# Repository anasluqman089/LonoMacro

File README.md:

# LonoMacro

LonoMacro is a modular macro keypad built around three XIAO nRF52840 boards:
an OLED-equipped master, a keypad slave, and a rotary-encoder slave. The master
connects to a computer over USB-C and to the slaves over Bluetooth Low Energy
(BLE). Slave inputs are forwarded to the computer as USB keyboard events.

## Project files

- [`PCB/`](PCB/) — KiCad schematic, PCB layout, and project files.
- [`CAD/`](CAD/) — 3D STEP models.
- [`Production/`](Production/) — Gerber, drill, and STL manufacturing files.
- [`firmware/`](firmware/) — Arduino sketches for the master and both slaves.
- [`BOM.csv`](BOM.csv) — Bill of materials, prices, and supplier search links.

## Firmware setup

Install the ArduinoBLE, Adafruit GFX, and Adafruit SSD1306 libraries. Select a
XIAO nRF52840 Arduino board package that supports USB keyboard output for the
master. Compile and upload the corresponding sketch to each board:

- [OLED master](firmware/OLED_Master/OLED_Master.ino)
- [Keypad slave](firmware/Keypad_Slave/Keypad_Slave.ino)
- [Rotary slave](firmware/Rotary_Slave/Rotary_Slave.ino)

The master expects an SSD1306 I2C OLED at address `0x3C`.

## Pairing and controls

1. Connect the OLED master to the computer over USB-C.
2. Press the 6 mm pairing button on each slave: SW5 on the keypad and SW7 on
   the rotary encoder. The corresponding slave LED blinks while it advertises.
3. Press the 6 mm pairing/connect button on the master (SW8). The master LED
   blinks while it searches, and the OLED shows each slave's connection status.
   When both slaves are connected, the master LED and both slave LEDs stay on.
4. Press SW1–SW4 to send the number keys `1`–`4`. Rotate the encoder to send
   Up/Down arrow keys; press the encoder (SW6) to send Enter.

The master LED is solid when both slaves are connected and pulses when it
receives an input. A connected slave LED is solid and pulses when it sends an
input. If a slave disconnects, press its pairing button and then press SW8 on
the master to reconnect.

## OLED and battery status

The OLED-equipped master is intended to show the connected macropads and their
battery levels. A future status screen could include the time and date, for
example:

```text
10:00 PM              1/11/26
----------------------------
Rotary Encoder          50%
Keypad                   5%
```

The current firmware displays connection status and recent input events; it
does not yet report slave battery levels or show a clock. Battery reporting and
time display will require additional firmware and, for the clock, a time source.
The master can be powered from the computer's USB-C connection. The slave
macropads are intended to use lithium-ion batteries; battery and charging
hardware should be selected to match the final design.

## Bill of materials

Prices are the listed prices per BOM row, including grouped quantities. They
are estimates, may change, and **do not include shipping**. The case price is
approximate; purchase links are supplier search pages.

| Component | Qty | Real Unit Price (USD) | Total Market Price (USD) | Reference Links |
| :--- | :---: | :---: | :---: | :--- |
| **XIAO-nRF52840** (Standard) | 3 | \$9.99 | **\$29.97** | [Search AliExpress](https://www.aliexpress.com/w/wholesale-XIAO-nRF52840.html) |
| **Cherry MX Keyboard Switch** | 4 | \$0.60 | **\$2.40** | [Search AliExpress](https://www.aliexpress.com/w/wholesale-Cherry-MX-keyboard-switch.html) |
| **1.3 Inch OLED Screen** | 1 | \$4.00 | **\$4.00** | [Search AliExpress](https://www.aliexpress.com/w/wholesale-1.3-Inch-OLED-Screen.html) |
| **Rotary Encoder EC11** | 1 | \$0.50 | **\$0.50** | [Search AliExpress](https://www.aliexpress.com/w/wholesale-Rotary-Encoder.html) |
| **5mm LED** | 3 | \$0.10 | **\$0.30** | [Search AliExpress](https://www.aliexpress.com/w/wholesale-5mm-LED.html) |
| **01x02 JST PH Connector** | 3 | \$0.15 | **\$0.45** | [Search AliExpress](https://www.aliexpress.com/w/wholesale-01x02-JST-PH-Connector.html) |
| **220 Film Resistor** | 3 | \$0.05 | **\$0.15** | [Search AliExpress](https://www.aliexpress.com/w/wholesale-220-Film-Resistor.html) |
| **6 mm THT Switch** | 3 | \$0.10 | **\$0.30** | [Search AliExpress](https://www.aliexpress.com/w/wholesale-6-mm-THT-switch.html) |
| **01x04 Pin Header** | 1 | \$0.20 | **\$0.20** | [Search AliExpress](https://www.aliexpress.com/w/wholesale-01x04-Pin-Header.html) |
| **PCB Fabrication** | 1 | \$12.00 | **\$12.00** | — |
| **3D Printed Case** | 1 | \$15.00 | **\$15.00** | — |
| **Estimated Real Total** | | | **~\$65.27** | |

## CAD

[Open the LonoMacro Onshape document](https://cad.onshape.com/documents/b238660379d2ad484aa23eea/w/9873678c9d89b1b19152732d/e/ca0627a1691ab6fd1505dec4).

## Image 

### Scematic

### PCB

### CAD

## Extra

This project is made for Fabricate, a YSWS program by Hack Club

[Project](https://fabricate.hackclub.com/projects/699).

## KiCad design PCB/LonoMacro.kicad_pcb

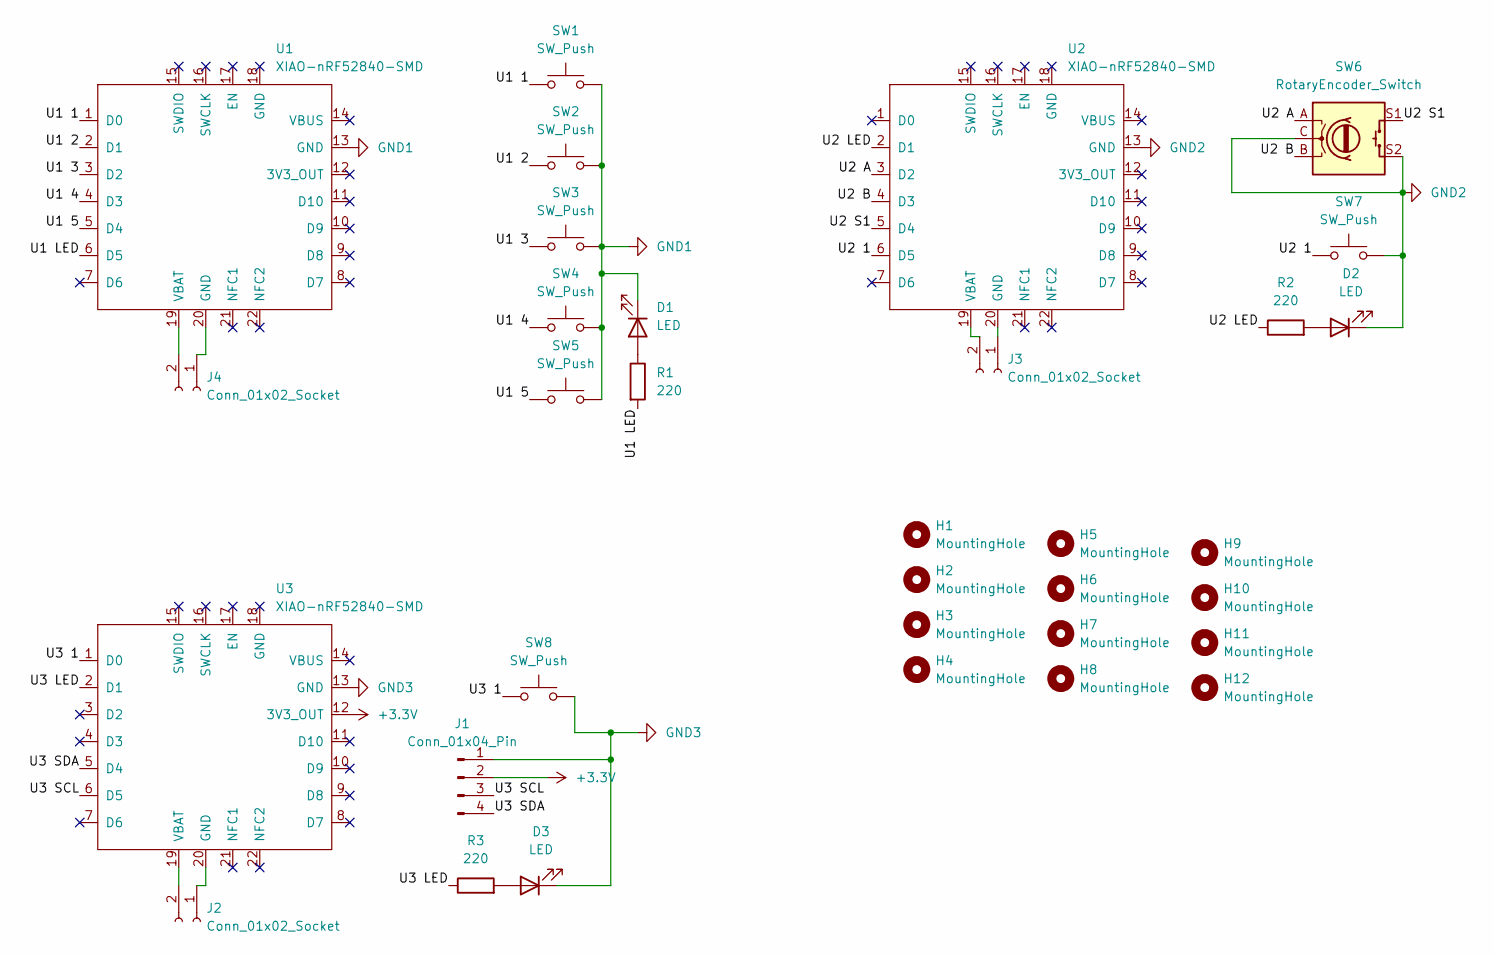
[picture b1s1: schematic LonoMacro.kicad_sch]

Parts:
D1, D2, D3: LED; LED_D5.0mm
H1, H2, H3, H4, H5, H6, H7, H8, H9, H10, H11, H12: MountingHole; MountingHole_2.2mm_M2
J1: Conn_01x04_Pin; PinHeader_1x04_P2.54mm_Vertical
J2, J3, J4: Conn_01x02_Socket; JST_PH_S2B-PH-K_1x02_P2.00mm_Horizontal
R1, R2, R3: 220; R_Axial_DIN0207_L6.3mm_D2.5mm_P7.62mm_Horizontal
SW1, SW2, SW3, SW4: SW_Push; SW_Cherry_MX_1.00u_PCB
SW5, SW7, SW8: SW_Push; SW_PUSH_6mm
SW6: RotaryEncoder_Switch; RotaryEncoder_Alps_EC11E-Switch_Vertical_H20mm
U1, U2, U3: XIAO-nRF52840-SMD

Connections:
+3.3V: J1.2, U3.12 (3V3_OUT)
/U1 1: SW1.1, U1.1 (D0)
/U1 2: SW2.1, U1.2 (D1)
/U1 3: SW3.1, U1.3 (D2)
/U1 4: SW4.1, U1.4 (D3)
/U1 5: SW5.1, U1.5 (D4)
/U1 LED: R1.2, U1.6 (D5)
/U2 1: SW7.1, U2.6 (D5)
/U2 A: SW6.A, U2.3 (D2)
/U2 B: SW6.B, U2.4 (D3)
/U2 LED: R2.1, U2.2 (D1)
/U2 S1: SW6.S1, U2.5 (D4)
/U3 1: SW8.1, U3.1 (D0)
/U3 LED: R3.1, U3.2 (D1)
/U3 SCL: J1.3, U3.6 (D5)
/U3 SDA: J1.4, U3.5 (D4)
GND1: D1.1 (K), SW1.2, SW2.2, SW3.2, SW4.2, SW5.2, U1.13 (GND)
GND2: D2.1 (K), SW6.C, SW6.S2, SW7.2, U2.13 (GND)
GND3: D3.1 (K), J1.1, SW8.2, U3.13 (GND)
unnamed: D1.2 (A), R1.1
unnamed: D2.2 (A), R2.2
unnamed: D3.2 (A), R3.2
unnamed: J2.1, U3.20 (GND)
unnamed: J2.2, U3.19 (VBAT)
unnamed: J3.1, U2.20 (GND)
unnamed: J3.2, U2.19 (VBAT)
unnamed: J4.1, U1.20 (GND)
unnamed: J4.2, U1.19 (VBAT)

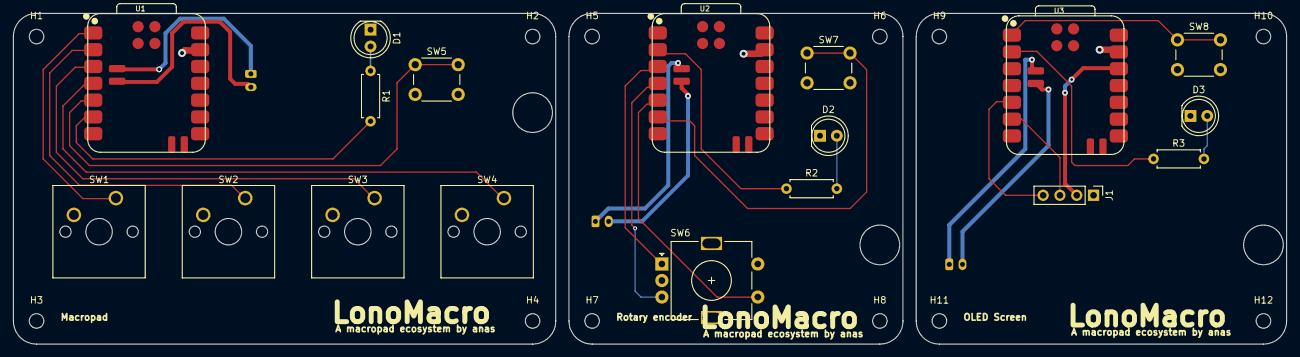
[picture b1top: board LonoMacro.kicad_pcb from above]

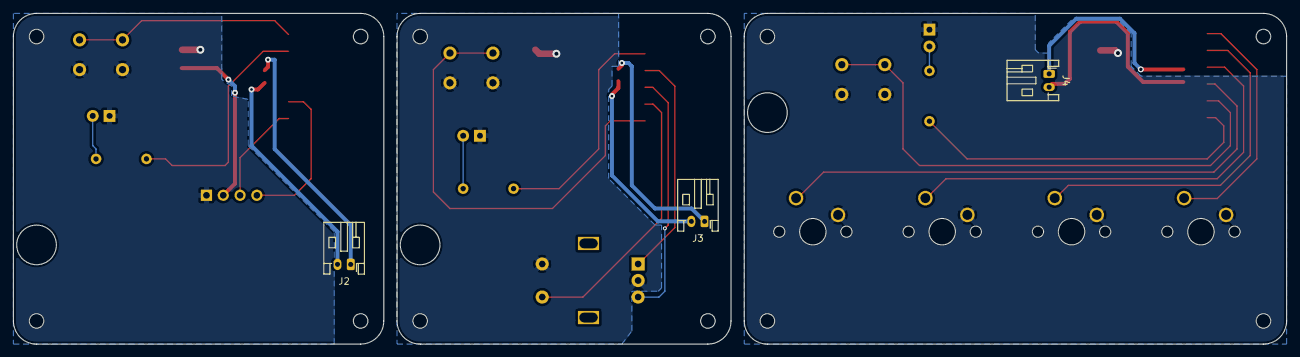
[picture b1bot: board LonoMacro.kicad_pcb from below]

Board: 2 copper layers, 192.5 x 50.0 mm, 33 parts (3 on the bottom side), 28 nets.

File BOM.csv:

"Reference","Quantity","Name","Price","Buy Link"
"D1,D2,D3","3","5mm LED","$0.30","https://www.aliexpress.com/w/wholesale-5mm-LED.html"
"J1","1","01x04 Pin Header","$0.20","https://www.aliexpress.com/w/wholesale-01x04-Pin-Header.html"
"J2,J3,J4","3","01x02 JST PH Connector","$0.45","https://www.aliexpress.com/w/wholesale-01x02-JST-PH-Connector.html"
"R1,R2,R3","3","220 Film Resistor","$0.15","https://www.aliexpress.com/w/wholesale-220-Film-Resistor.html"
"SW1,SW2,SW3,SW4","4","Cherry MX keyboard switch","$1.00","https://www.aliexpress.com/w/wholesale-Cherry-MX-keyboard-sw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"
"SW5,SW7,SW8","3","6 mm THT switch","$0.30","https://www.aliexpress.com/w/wholesale-6-mm-THT-switch.html"
"SW6","1","Rotary Encoder","$0.30","https://www.aliexpress.com/w/wholesale-Rotary-Encoder.html"
"U1,U2,U3","3","XIAO-nRF52840","$5.00","https://www.aliexpress.com/w/wholesale-XIAO-nRF52840.html"
"-","1","1.3 Inch OLED Screen","$10.00","https://www.aliexpress.com/w/wholesale-1.3-Inch-OLED-Screen.html"
"-","1","PCB","$12.00","-"	
"-","1","3D Printed Case","~$15.00","-"
"","","Total","~$44.70"
